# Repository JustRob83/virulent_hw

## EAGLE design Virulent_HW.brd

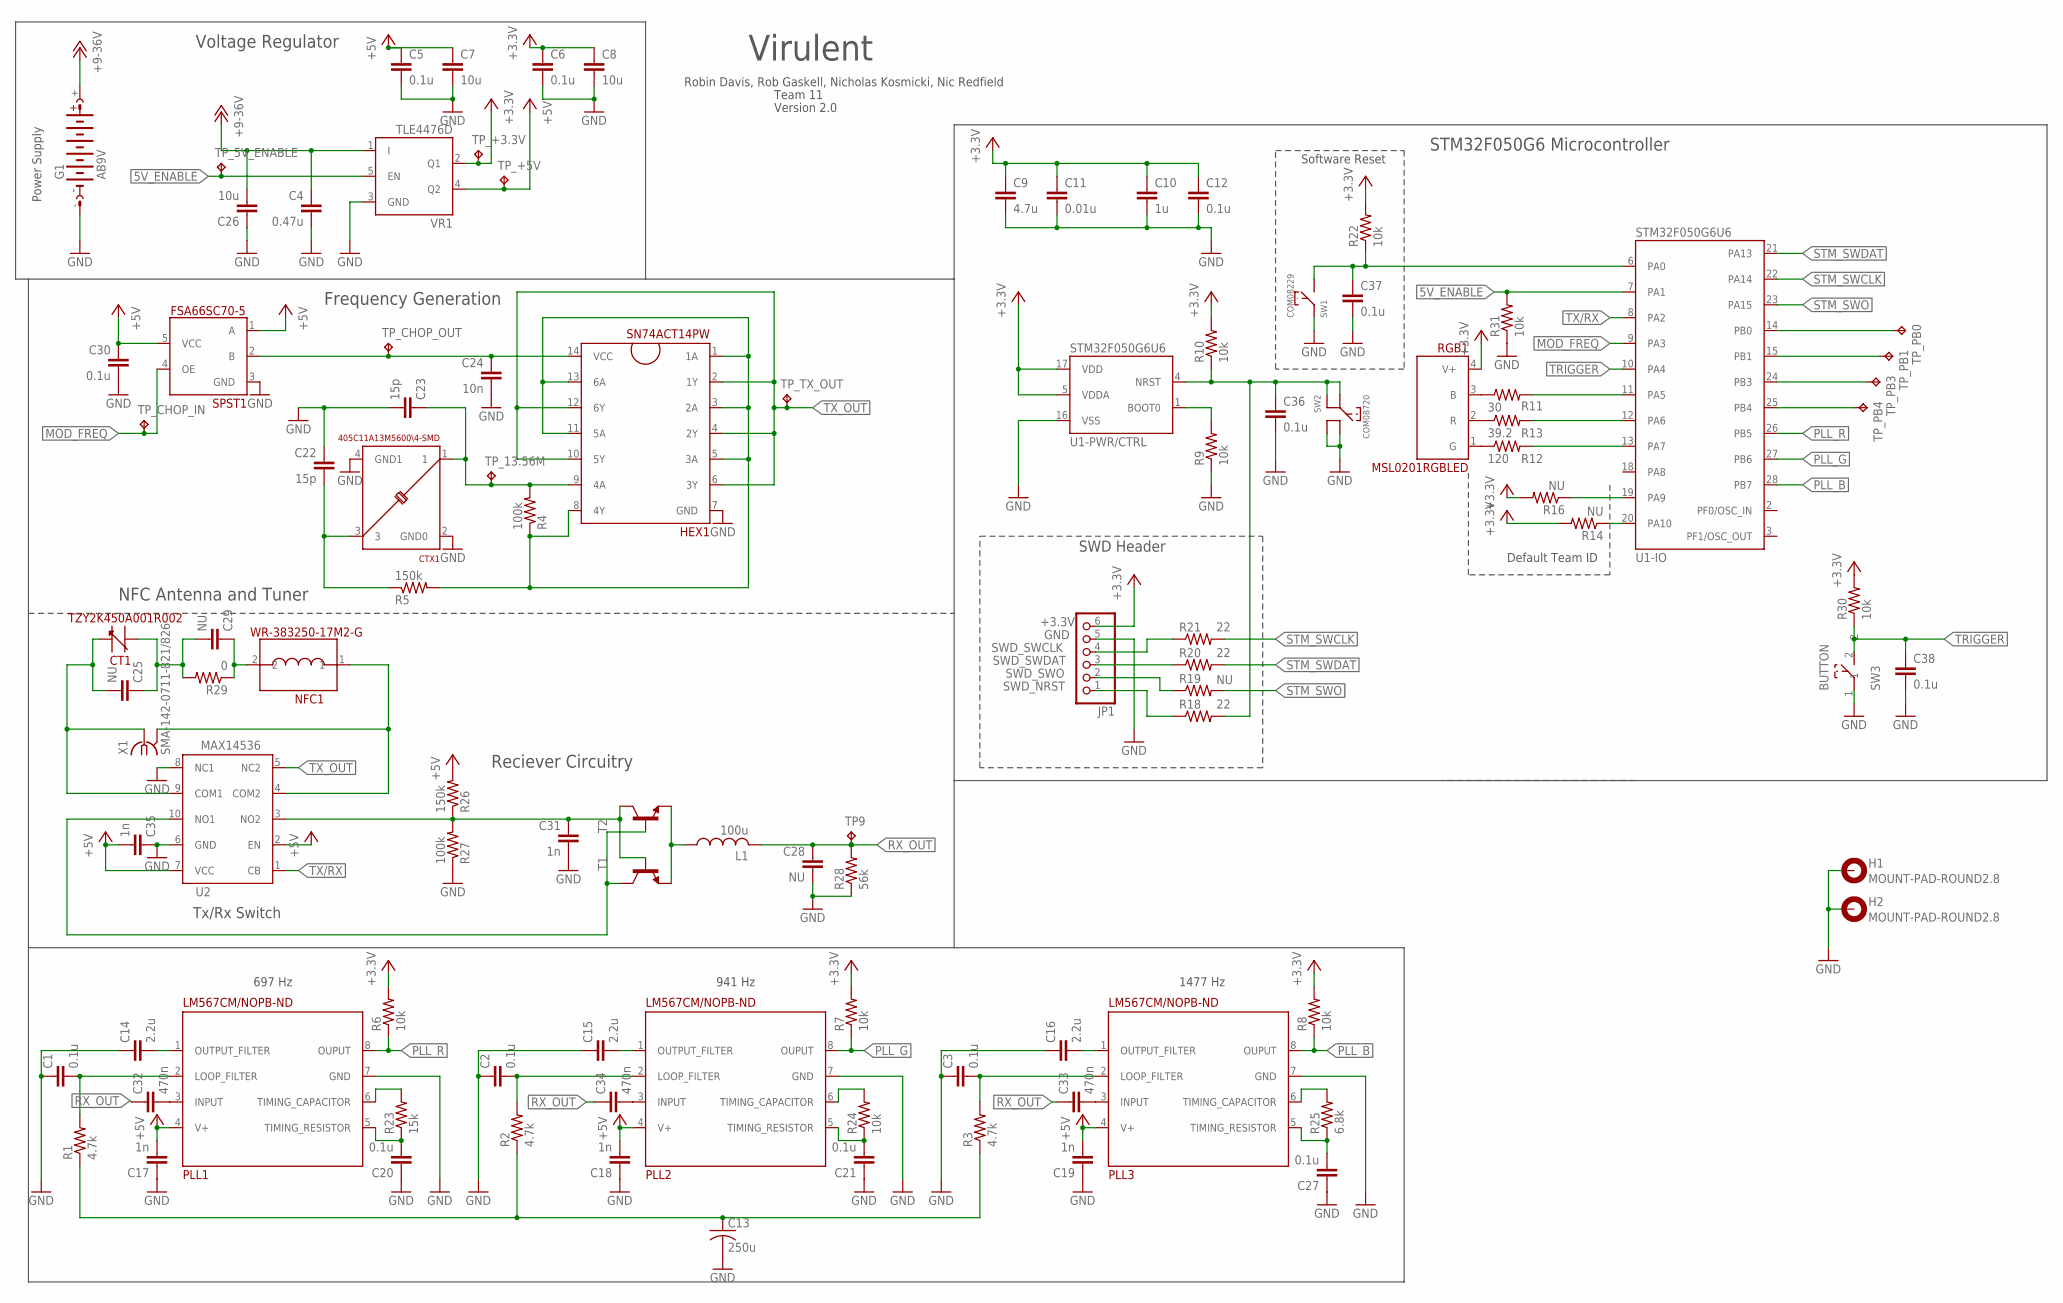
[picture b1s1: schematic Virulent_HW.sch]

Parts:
C1, C2, C3, C5, C6, C12, C20, C21, C27, C30: 0.1u; C0402
C4: 0.47u; C1206
C7, C8, C26: 10u; C1206
C9: 4.7u; C0805
C10: 1u; C0805
C11: 0.01u; C0402
C13: 250u; C1210
C14, C15, C16: 2.2u; C0402
C17, C18, C19, C31, C35: 1n; C0402
C22, C23: 15p; C0402
C24: 10n; C0402
C25, C28, C29: NU; C0402
C32, C33, C34: 470n; C0402
C36, C37, C38: 0.1u; C0603
CT1: TZY2K450A001R002; TZY2
CTX1: 405C11A13M5600\4-SMD; 4-SMD
G1: AB9V
H1, H2: MOUNT-PAD-ROUND2.8; 2,8-PAD
HEX1: SN74ACT14PW; TSSOP14
JP1: PINHD-1X6; 1X06
L1: 100u; L1008
NFC1: WR-383250-17M2-G; 17M2-G
PLL1, PLL2, PLL3: LM567CM/NOPB-ND; SOIC-8
R1, R2, R3: 4.7k; R0402
R4, R27: 100k; R0402
R5, R26: 150k; R0402
R6, R7, R8, R9, R10, R22, R24, R30, R31: 10k; R0402
R11: 30; R0402
R12: 120; R0402
R13: 39.2; R0402
R14, R16, R19: NU; R0402
R18, R20, R21: 22; R0402
R23: 15k; R0402
R25: 6.8k; R0402
R28: 56k; R0402
R29: 0; R0402
RGB1: MSL0201RGBLED; MSL0201RGB
SPST1: FSA66SC70-5; 6-TSSOP
SW1: COM08229
SW2: COM08720
SW3: BUTTON; 17M2-G
T1, T2: 2N2222-NPN-TO18-EBC; TO18
TP9: TPTP06SQ; TP06SQ
TP_5V_ENABLE, TP_13.56M: TPTP06SQ; TP06SQ
TP_+3.3V, TP_+5V: TPTP06SQ; TP06SQ
TP_CHOP_IN: TPTP06SQ; TP06SQ
TP_CHOP_OUT: TPTP06SQ; TP06SQ
TP_PB0, TP_PB1, TP_PB3, TP_PB4: TPTP06SQ; TP06SQ
TP_TX_OUT: TPTP06SQ; TP06SQ
U1: STM32F050G6U6; UQFPN-28
U2: MAX14536; 10UTQFN
VR1: TLE4476D; PG-TO252-5-11
X1: SMA-142-0711-821/826; J502-ND-142-0711-821/826

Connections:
5V_ENABLE: R31.2, TP_5V_ENABLE.TP, U1.7 (PA1), VR1.5 (EN)
+2V: C31.1, R26.1, R27.2, T1.3 (C), T2.2 (B), U2.3 (NO2)
+3.3V: C6.1, C8.1, C9.1, C10.1, C11.1, C12.1, JP1.6, R6.2, R7.2, R8.2, R10.2, R14.2, R16.2, R22.2, R30.2, RGB1.4 (V+), TP_+3.3V.TP, U1.5 (VDDA), U1.17 (VDD), VR1.2 (Q1)
+5V: C5.1, C7.1, C17.2, C18.2, C19.2, C30.1, C35.2, PLL1.4 (V+), PLL2.4 (V+), PLL3.4 (V+), R26.2, SPST1.1 (A), SPST1.5 (VCC), TP_+5V.TP, U2.2 (EN), U2.7 (VCC), VR1.4 (Q2)
+9-36V: C4.1, C26.2, G1.+, VR1.1 (I)
CHOPPED_FREQ: C24.1, HEX1.14 (VCC), SPST1.2 (B), TP_CHOP_OUT.TP
GND: C1.1, C2.1, C3.1, C4.2, C5.2, C6.2, C7.2, C8.2, C9.2, C10.2, C11.2, C12.2, C13.2, C14.1, C15.1, C16.1, C17.1, C18.1, C19.1, C20.1, C21.1, C22.1, C23.2, C24.2, C26.1, C27.1, C28.2, C30.2, C31.2, C35.1, C36.2, C37.2, C38.2, CTX1.2 (GND0), CTX1.4 (GND1), G1.-, H1.B2,8, H2.B2,8, HEX1.7 (GND), JP1.5, PLL1.7 (GND), PLL2.7 (GND), PLL3.7 (GND), R9.1, R27.1, R28.1, R31.1, SPST1.3 (GND), SW1.1, SW2.3, SW2.4, SW3.1, U1.16 (VSS), U2.6 (GND), U2.8 (NC1), VR1.3 (GND)
MOD_FREQ: SPST1.4 (OE), TP_CHOP_IN.TP, U1.9 (PA3)
unnamed: C1.2, PLL1.2 (LOOP_FILTER), R1.2
unnamed: C2.2, PLL2.2 (LOOP_FILTER), R2.2
unnamed: C3.2, PLL3.2 (LOOP_FILTER), R3.2
unnamed: C13.1, R1.1, R2.1, R3.1
unnamed: C14.2, PLL1.1 (OUTPUT_FILTER)
unnamed: C36.1, R10.1, R18.2, SW2.1, SW2.2, U1.4 (NRST)
unnamed: C16.2, PLL3.1 (OUTPUT_FILTER)
unnamed: C20.2, PLL1.5 (TIMING_RESISTOR), R23.1
unnamed: R9.2, U1.1 (BOOT0)
unnamed: C15.2, PLL2.1 (OUTPUT_FILTER)
unnamed: C21.2, PLL2.5 (TIMING_RESISTOR), R24.1
unnamed: PLL1.6 (TIMING_CAPACITOR), R23.2
unnamed: PLL2.6 (TIMING_CAPACITOR), R24.2
unnamed: C32.2, PLL1.3 (INPUT)
unnamed: C27.2, PLL3.5 (TIMING_RESISTOR), R25.1
unnamed: C23.1, CTX1.1, HEX1.9 (4A), R4.2, TP_13.56M.TP
unnamed: C25.2, CT1.2 (B), U2.9 (COM1), X1.1
unnamed: R11.1, RGB1.3 (B)
unnamed: T1.2 (B), T2.3 (C), U2.10 (NO1)
unnamed: C34.2, PLL2.3 (INPUT)
unnamed: HEX1.1 (1A), HEX1.3 (2A), HEX1.5 (3A), HEX1.8 (4Y), HEX1.11 (5A), HEX1.13 (6A), R4.1, R5.2
unnamed: C33.2, PLL3.3 (INPUT)
unnamed: C25.1, C29.2, CT1.1 (A), R29.2
unnamed: PLL3.6 (TIMING_CAPACITOR), R25.2
unnamed: R11.2, U1.11 (PA5)
unnamed: R13.2, U1.12 (PA6)
unnamed: C29.1, NFC1.2, R29.1
unnamed: R12.2, U1.13 (PA7)
unnamed: NFC1.1, U2.4 (COM2), X1.G@1 (2), X1.G@2 (2), X1.G@3 (2), X1.G@4 (2)
unnamed: C22.2, CTX1.3, R5.1
unnamed: R16.1, U1.19 (PA9)
unnamed: R12.1, RGB1.1 (G)
unnamed: R13.1, RGB1.2 (R)
unnamed: TP_PB4.TP, U1.25 (PB4)
NRESET_SOFT: C37.1, R22.1, SW1.2, U1.6 (PA0)
PB0: TP_PB0.TP, U1.14 (PB0)
PB1: TP_PB1.TP, U1.15 (PB1)
PB3: TP_PB3.TP, U1.24 (PB3)
PLL_B: PLL3.8 (OUPUT), R8.1, U1.28 (PB7)
PLL_G: PLL2.8 (OUPUT), R7.1, U1.27 (PB6)
PLL_R: PLL1.8 (OUPUT), R6.1, U1.26 (PB5)
RX_OUT: C28.1, C32.1, C33.1, C34.1, L1.2, R28.2, TP9.TP
RX_OUT_L: L1.1, T1.1 (E), T2.1 (E)
STM_SWCLK: R21.2, U1.22 (PA14)
STM_SWDAT: R20.2, U1.21 (PA13)
STM_SWO: R19.2, U1.23 (PA15)
SWD_NRST: JP1.1, R18.1
SWD_SWCLK: JP1.4, R21.1
SWD_SWDAT: JP1.3, R20.1
SWD_SWO: JP1.2, R19.1
TEAMID1: R14.1, U1.20 (PA10)
TRIGGER: C38.1, R30.1, SW3.2, U1.10 (PA4)
TX/RX: U1.8 (PA2), U2.1 (CB)
TX_OUT: HEX1.2 (1Y), HEX1.4 (2Y), HEX1.6 (3Y), HEX1.10 (5Y), HEX1.12 (6Y), TP_TX_OUT.TP, U2.5 (NC2)

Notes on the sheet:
Voltage Regulator
STM32F050G6 Microcontroller
Default Team ID
Power Supply
Virulent
Robin Davis, Rob Gaskell, Nicholas Kosmicki, Nic Redfield
Team 11
Version 2.0
SWD Header
697 Hz
941 Hz
1477 Hz
Software Reset
Frequency Generation
NFC Antenna and Tuner
Reciever Circuitry
Tx/Rx Switch

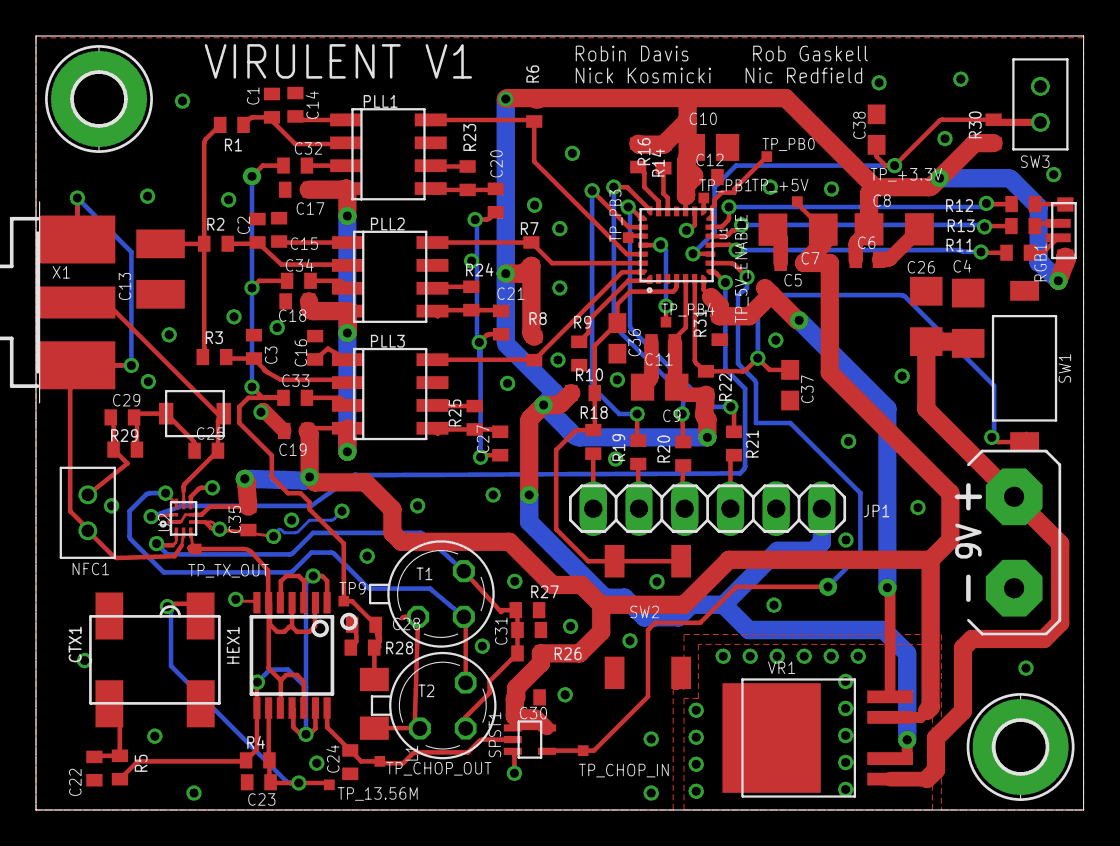
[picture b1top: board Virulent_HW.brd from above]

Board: 2 copper layers, 58.2 x 43.0 mm, 102 parts (0 on the bottom side), 62 nets.

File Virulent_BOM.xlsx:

Partlist exported from C:/Users/Rob/Projects/Virulent_HW/Virulent_HW.sch at 11/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
Qty | Qty_Ext | Value | Device | Package | Part Number to Order | Parts | Description
2 | 24 |  | 2N2222-NPN-TO18-EBC | TO18 |  | T1, T2 | NPN Transistror
1 | 12 |  | PINHD-1X6 | 1X06 |  | JP1 | PIN HEADER
1 | 12 | 0 | R-US_R0402 | R0402 |  | R29 | RESISTOR, American symbol
1 | 12 | 0.01u | C-EUC0402 | C0402 |  | C11 | CAPACITOR, European symbol
10 | 120 | 0.1u | C-EUC0402 | C0402 |  | C1, C2, C3, C5, C6, C12, C20, C21, C27, C30 | CAPACITOR, European symbol
3 | 36 | 0.1u | C-EUC0603 | C0603 |  | C36, C37, C38 | CAPACITOR, European symbol
1 | 12 | 0.47u | C-EUC1206 | C1206 |  | C4 | CAPACITOR, European symbol
2 | 24 | 100k | R-US_R0402 | R0402 |  | R4, R27 | RESISTOR, American symbol
1 | 12 | 100u | L-USL1008 | L1008 |  | L1 | INDUCTOR, American symbol
9 | 108 | 10k | R-US_R0402 | R0402 |  | R6, R7, R8, R9, R10, R22, R24, R30, R31 | RESISTOR, American symbol
1 | 12 | 10n | C-EUC0402 | C0402 |  | C24 | CAPACITOR, European symbol
3 | 36 | 10u | C-EUC1206 | C1206 |  | C7, C8, C26 | CAPACITOR, European symbol
1 | 12 | 120 | R-US_R0402 | R0402 |  | R12 | RESISTOR, American symbol
2 | 24 | 150k | R-US_R0402 | R0402 |  | R5, R26 | RESISTOR, American symbol
1 | 12 | 15k | R-US_R0402 | R0402 |  | R23 | RESISTOR, American symbol
2 | 24 | 15p | C-EUC0402 | C0402 |  | C22, C23 | CAPACITOR, European symbol
5 | 60 | 1n | C-EUC0402 | C0402 |  | C17, C18, C19, C31, C35 | CAPACITOR, European symbol
1 | 12 | 1u | C-EUC0805 | C0805 |  | C10 | CAPACITOR, European symbol
3 | 36 | 2.2u | C-EUC0402 | C0402 |  | C14, C15, C16 | CAPACITOR, European symbol
3 | 36 | 22 | R-US_R0402 | R0402 |  | R18, R20, R21 | RESISTOR, American symbol
1 | 12 | 250u | C-USC1210 | C1210 |  | C13 | CAPACITOR, American symbol
1 | 12 | 30 | R-US_R0402 | R0402 |  | R11 | RESISTOR, American symbol
1 | 12 | 39.200000000000003 | R-US_R0402 | R0402 |  | R13 | RESISTOR, American symbol
3 | 36 | 4.7k | R-US_R0402 | R0402 |  | R1, R2, R3 | RESISTOR, American symbol
1 | 12 | 4.7u | C-EUC0805 | C0805 |  | C9 | CAPACITOR, European symbol
1 | 12 | 405C11A13M5600\4-SMD | 405C11A13M5600\4-SMD | 4-SMD |  | CTX1
3 | 36 | 470n | C-EUC0402 | C0402 |  | C32, C33, C34 | CAPACITOR, European symbol
1 | 12 | 56k | R-US_R0402 | R0402 |  | R28 | RESISTOR, American symbol
1 | 12 | 6.8k | R-US_R0402 | R0402 |  | R25 | RESISTOR, American symbol
1 | 12 | AB9V | AB9V | AB9V |  | G1 | 9-V BATTERY CLIP
1 | 12 | BUTTON | BUTTON | 17M2-G |  | SW3
1 | 12 | COM08229 | COM08229 | COM08229 |  | SW1
1 | 12 | COM08720 | COM08720 | COM08720 |  | SW2
1 | 12 | FSA66SC70-5 | FSA66SC70-5 | 6-TSSOP |  | SPST1
3 | 36 | LM567CM/NOPB-ND | LM567CM/NOPB-ND | SOIC-8 |  | PLL1, PLL2, PLL3
1 | 12 | MAX14536 | MAX14536 | 10UTQFN |  | U2
2 | 24 | MOUNT-PAD-ROUND2.8 | MOUNT-PAD-ROUND2.8 | 2,8-PAD |  | H1, H2 | MOUNTING PAD, round
1 | 12 | MSL0201RGBLED | MSL0201RGBLED | MSL0201RGB |  | RGB1
3 | 36 | NU | C-EUC0402 | C0402 |  | C25, C28, C29 | CAPACITOR, European symbol
3 | 36 | NU | R-US_R0402 | R0402 |  | R14, R16, R19 | RESISTOR, American symbol
1 | 12 | SMA-142-0711-821/826 | SMA-142-0711-821/826 | J502-ND-142-0711-821/826 |  | X1 | SMA 50 Ohm End Launch Jack Receptacle - Round Contact
1 | 12 | SN74ACT14PW | SN74ACT14PW | TSSOP14 |  | HEX1
1 | 12 | STM32F050G6U6 | STM32F050G6U6 | UQFPN-28 |  | U1
1 | 12 | TLE4476D | TLE4476D | PG-TO252-5-11 |  | VR1
1 | 12 | TZY2K450A001R002 | TZY2K450A001R002 | TZY2 |  | CT1
1 | 12 | WR-383250-17M2-G | WR-383250-17M2-G | 17M2-G |  | NFC1

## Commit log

2013-10-27 Initial Check-in
2013-10-28 Added Virulent_HW library for project components.
2013-10-28 Fixed unused library errors.
2013-10-30 Created PLLs and added them to schematic
2013-10-30 Added datasheets folder. Added power supply to schematic.
2013-10-31 Added RGB LED (MSL0201RGB) and Hex Inverter (SN74ACT14) to library. Updated PLL circuitry in schematic.
2013-10-31 Added crystal oscillator to library. Added carrier frequency circuitry to schematic.
2013-10-31 Added uC and LED to schematic.
2013-11-03 Added the following components to library: SPST Switch, NFC Coil, Variable Capacitor. Updated circuitry to include NFC coil and tuning, initial state circuitry, and frequency modulation. Added approp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
2013-11-04 updated LED symbol
2013-11-04 added no place capcitor to NFC coil transmitter in case needed
2013-11-05 updated power symbol and a few revisions suggested by Andrew. Added team information.
2013-11-09 Power supply updated as well as some changes suggested by Andrew
2013-11-10 Added SWD connector, Bulk input capacitance.
2013-11-12 Updated reciever and PLL circuitry. Added hard and soft reset buttons.
2013-11-12 updated package size for 250y Capacitor
2013-11-12 Updated uC pinout.
2013-11-12 updated cap sizes. Started to mess with board layour but did not accomplish very much.
2013-11-12 messed around with PCB layout
2013-11-14 First Draft of PCB. Changes made to reciever of schematic per Nic's instructions.Changed LED pins to better suit routing needs. Added dpdt switch to change nfc coil from tx/rx, to be controlled by mi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
2013-11-14 minor changes made to schematic for primarily esthetic reasons. Changed Version number to 2.0
2013-11-15 Added gitignore file.
2013-11-15 Added extensions.
2013-11-15 Removed .epf file from repo.
2013-11-17 Moved LDO, resized vias.
2013-11-17 L1 needs to be remade, need SMA conn added to pin 4/pin9 of U2.
2013-11-17 fixed library
2013-11-18 fixed L1008 part. rearranged board. added SMA connector.
2013-11-18 Added thermal isolation for LDO.
2013-11-18 added drc error files
2013-11-18 Added mount holes, completed layout.
2013-11-18 modified silkscreen
2013-11-19 Connected mounting holes to GND.
2013-11-20 Removed stop mask from vias.
2013-11-22 Generated BOM.
2013-11-22 Added MS Office-generated system files to ignore.
2013-11-24 Initial check-in.
2013-12-03 updated excel bom
2013-12-03 Added Item# column for bag markings.
